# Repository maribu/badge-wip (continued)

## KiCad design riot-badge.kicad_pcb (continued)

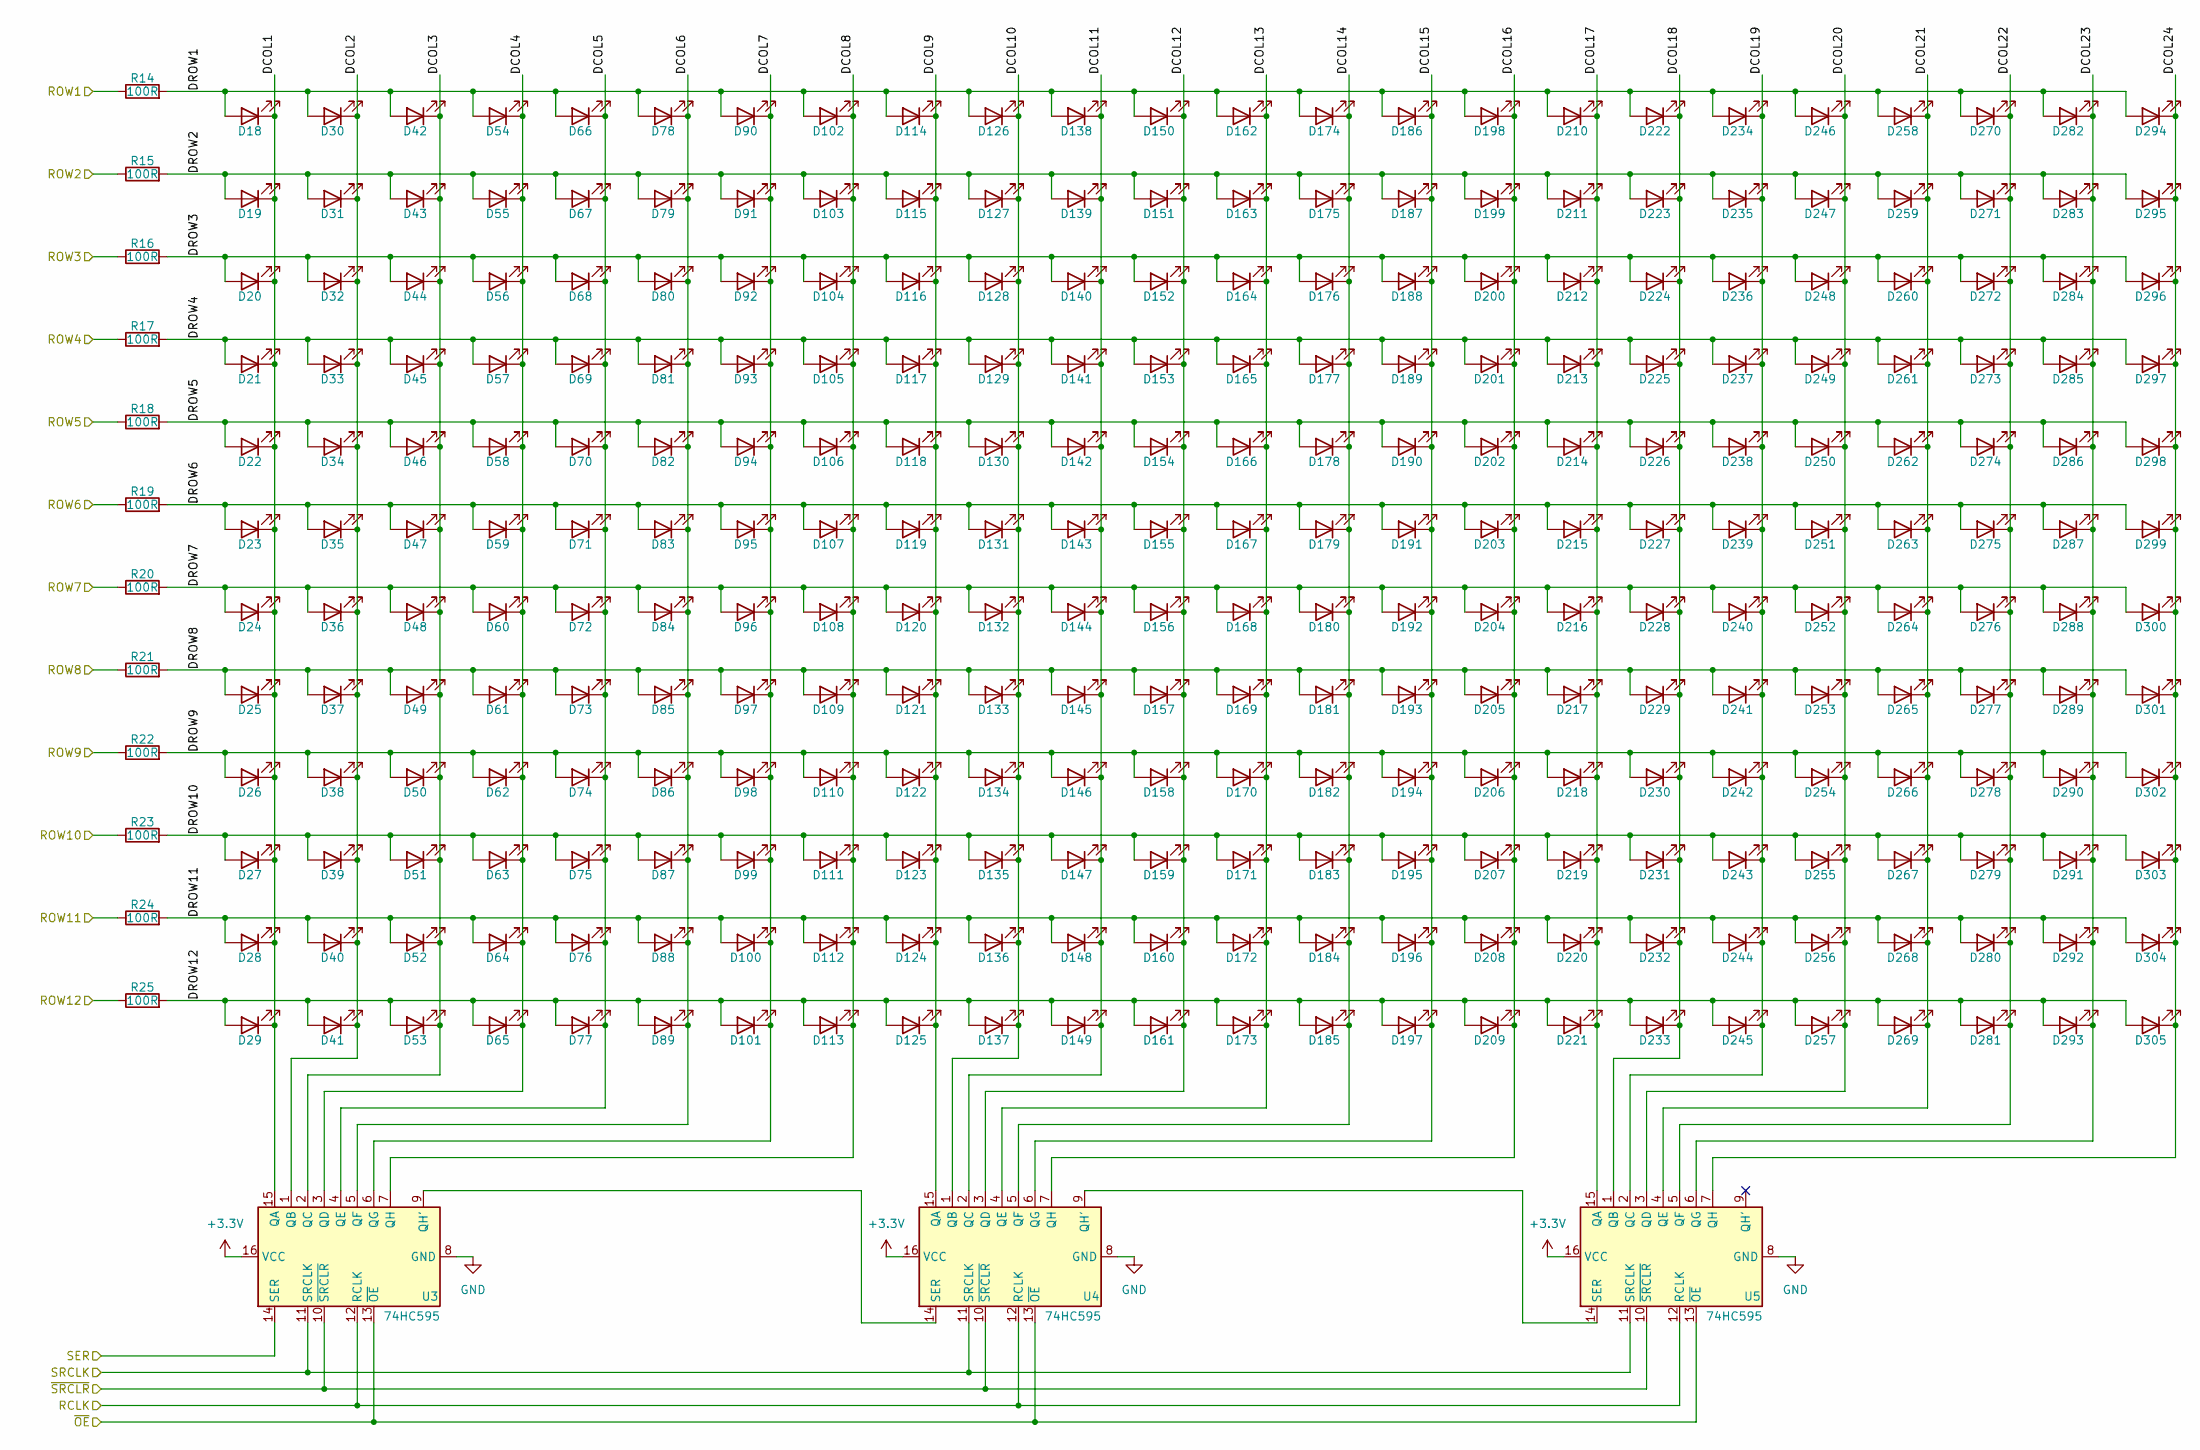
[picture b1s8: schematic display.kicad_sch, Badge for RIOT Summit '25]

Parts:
D18, D19, D20, D21, D22, D23, D24, D25, D26, D27, D28, D29, D30, D31, D32, D33, D34, D35, D36, D37, D38, D39, D40, D41, D42, D43, D44, D45, D46, D47, D48, D49, D50, D51, D52, D53, D54, D55, D56, D57, D58, D59, D60, D61, D62, D63, D64, D65, D66, D67, D68, D69, D70, D71, D72, D73, D74, D75, D76, D77, D78, D79, D80, D81, D82, D83, D84, D85, D86, D87, D88, D89, D90, D91, D92, D93, D94, D95, D96, D97, D98, D99, D100, D101, D102, D103, D104, D105, D106, D107, D108, D109, D110, D111, D112, D113, D114, D115, D116, D117, D118, D119, D120, D121, D122, D123, D124, D125, D126, D127, D128, D129, D130, D131, D132, D133, D134, D135, D136, D137, D138, D139, D140, D141, D142, D143, D144, D145, D146, D147, D148, D149, D150, D151, D152, D153, D154, D155, D156, D157, D158, D159, D160, D161, D162, D163, D164, D165, D166, D167, D168, D169, D170, D171, D172, D173, D174, D175, D176, D177, D178, D179, D180, D181, D182, D183, D184, D185, D186, D187, D188, D189, D190, D191, D192, D193, D194, D195, D196, D197, D198, D199, D200, D201, D202, D203, D204, D205, D206, D207, D208, D209, D210, D211, D212, D213, D214, D215, D216, D217, D218, D219, D220, D221, D222, D223, D224, D225, D226, D227, D228, D229, D230, D231, D232, D233, D234, D235, D236, D237, D238, D239, D240, D241, D242, D243, D244, D245, D246, D247, D248, D249, D250, D251, D252, D253, D254, D255, D256, D257, D258, D259, D260, D261, D262, D263, D264, D265, D266, D267, D268, D269, D270, D271, D272, D273, D274, D275, D276, D277, D278, D279, D280, D281, D282, D283, D284, D285, D286, D287, D288, D289, D290, D291, D292, D293, D294, D295, D296, D297, D298, D299, D300, D301, D302, D303, D304, D305: LED-White; LED_0603_1608Metric; LCSC C2290
R14, R15, R16, R17, R18, R19, R20, R21, R22, R23, R24, R25: 100R; R_0402_1005Metric; LCSC C25076
U3, U4, U5: 74HC595; SOIC-16_3.9x9.9mm_P1.27mm; LCSC C5947

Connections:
+3.3V: U3.16 (VCC), U4.16 (VCC), U5.16 (VCC); also elsewhere on the board
/DISP_RCLK: U3.12 (RCLK), U4.12 (RCLK), U5.12 (RCLK); also elsewhere on the board
/DISP_ROW1: R14.1; also elsewhere on the board
/DISP_ROW2: R15.1; also elsewhere on the board
/DISP_ROW3: R16.1; also elsewhere on the board
/DISP_ROW4: R17.1; also elsewhere on the board
/DISP_ROW5: R18.1; also elsewhere on the board
/DISP_ROW6: R19.1; also elsewhere on the board
/DISP_ROW7: R20.1; also elsewhere on the board
/DISP_ROW8: R21.1; also elsewhere on the board
/DISP_ROW9: R22.1; also elsewhere on the board
/DISP_ROW10: R23.1; also elsewhere on the board
/DISP_ROW11: R24.1; also elsewhere on the board
/DISP_ROW12: R25.1; also elsewhere on the board
/DISP_SER: U3.14 (SER); also elsewhere on the board
/DISP_SRCLK: U3.11 (SRCLK), U4.11 (SRCLK), U5.11 (SRCLK); also elsewhere on the board
/DISP_~SRCLR: U3.10 (~SRCLR), U4.10 (~SRCLR), U5.10 (~SRCLR); also elsewhere on the board
/Display/DCOL1: D18.1 (K), D19.1 (K), D20.1 (K), D21.1 (K), D22.1 (K), D23.1 (K), D24.1 (K), D25.1 (K), D26.1 (K), D27.1 (K), D28.1 (K), D29.1 (K), U3.15 (QA)
/Display/DCOL2: D30.1 (K), D31.1 (K), D32.1 (K), D33.1 (K), D34.1 (K), D35.1 (K), D36.1 (K), D37.1 (K), D38.1 (K), D39.1 (K), D40.1 (K), D41.1 (K), U3.1 (QB)
/Display/DCOL3: D42.1 (K), D43.1 (K), D44.1 (K), D45.1 (K), D46.1 (K), D47.1 (K), D48.1 (K), D49.1 (K), D50.1 (K), D51.1 (K), D52.1 (K), D53.1 (K), U3.2 (QC)
/Display/DCOL4: D54.1 (K), D55.1 (K), D56.1 (K), D57.1 (K), D58.1 (K), D59.1 (K), D60.1 (K), D61.1 (K), D62.1 (K), D63.1 (K), D64.1 (K), D65.1 (K), U3.3 (QD)
/Display/DCOL5: D66.1 (K), D67.1 (K), D68.1 (K), D69.1 (K), D70.1 (K), D71.1 (K), D72.1 (K), D73.1 (K), D74.1 (K), D75.1 (K), D76.1 (K), D77.1 (K), U3.4 (QE)
/Display/DCOL6: D78.1 (K), D79.1 (K), D80.1 (K), D81.1 (K), D82.1 (K), D83.1 (K), D84.1 (K), D85.1 (K), D86.1 (K), D87.1 (K), D88.1 (K), D89.1 (K), U3.5 (QF)
/Display/DCOL7: D90.1 (K), D91.1 (K), D92.1 (K), D93.1 (K), D94.1 (K), D95.1 (K), D96.1 (K), D97.1 (K), D98.1 (K), D99.1 (K), D100.1 (K), D101.1 (K), U3.6 (QG)
/Display/DCOL8: D102.1 (K), D103.1 (K), D104.1 (K), D105.1 (K), D106.1 (K), D107.1 (K), D108.1 (K), D109.1 (K), D110.1 (K), D111.1 (K), D112.1 (K), D113.1 (K), U3.7 (QH)
/Display/DCOL9: D114.1 (K), D115.1 (K), D116.1 (K), D117.1 (K), D118.1 (K), D119.1 (K), D120.1 (K), D121.1 (K), D122.1 (K), D123.1 (K), D124.1 (K), D125.1 (K), U4.15 (QA)
/Display/DCOL10: D126.1 (K), D127.1 (K), D128.1 (K), D129.1 (K), D130.1 (K), D131.1 (K), D132.1 (K), D133.1 (K), D134.1 (K), D135.1 (K), D136.1 (K), D137.1 (K), U4.1 (QB)
/Display/DCOL11: D138.1 (K), D139.1 (K), D140.1 (K), D141.1 (K), D142.1 (K), D143.1 (K), D144.1 (K), D145.1 (K), D146.1 (K), D147.1 (K), D148.1 (K), D149.1 (K), U4.2 (QC)
/Display/DCOL12: D150.1 (K), D151.1 (K), D152.1 (K), D153.1 (K), D154.1 (K), D155.1 (K), D156.1 (K), D157.1 (K), D158.1 (K), D159.1 (K), D160.1 (K), D161.1 (K), U4.3 (QD)
/Display/DCOL13: D162.1 (K), D163.1 (K), D164.1 (K), D165.1 (K), D166.1 (K), D167.1 (K), D168.1 (K), D169.1 (K), D170.1 (K), D171.1 (K), D172.1 (K), D173.1 (K), U4.4 (QE)
/Display/DCOL14: D174.1 (K), D175.1 (K), D176.1 (K), D177.1 (K), D178.1 (K), D179.1 (K), D180.1 (K), D181.1 (K), D182.1 (K), D183.1 (K), D184.1 (K), D185.1 (K), U4.5 (QF)
/Display/DCOL15: D186.1 (K), D187.1 (K), D188.1 (K), D189.1 (K), D190.1 (K), D191.1 (K), D192.1 (K), D193.1 (K), D194.1 (K), D195.1 (K), D196.1 (K), D197.1 (K), U4.6 (QG)
/Display/DCOL16: D198.1 (K), D199.1 (K), D200.1 (K), D201.1 (K), D202.1 (K), D203.1 (K), D204.1 (K), D205.1 (K), D206.1 (K), D207.1 (K), D208.1 (K), D209.1 (K), U4.7 (QH)
/Display/DCOL17: D210.1 (K), D211.1 (K), D212.1 (K), D213.1 (K), D214.1 (K), D215.1 (K), D216.1 (K), D217.1 (K), D218.1 (K), D219.1 (K), D220.1 (K), D221.1 (K), U5.15 (QA)
/Display/DCOL18: D222.1 (K), D223.1 (K), D224.1 (K), D225.1 (K), D226.1 (K), D227.1 (K), D228.1 (K), D229.1 (K), D230.1 (K), D231.1 (K), D232.1 (K), D233.1 (K), U5.1 (QB)
/Display/DCOL19: D234.1 (K), D235.1 (K), D236.1 (K), D237.1 (K), D238.1 (K), D239.1 (K), D240.1 (K), D241.1 (K), D242.1 (K), D243.1 (K), D244.1 (K), D245.1 (K), U5.2 (QC)
/Display/DCOL20: D246.1 (K), D247.1 (K), D248.1 (K), D249.1 (K), D250.1 (K), D251.1 (K), D252.1 (K), D253.1 (K), D254.1 (K), D255.1 (K), D256.1 (K), D257.1 (K), U5.3 (QD)
/Display/DCOL21: D258.1 (K), D259.1 (K), D260.1 (K), D261.1 (K), D262.1 (K), D263.1 (K), D264.1 (K), D265.1 (K), D266.1 (K), D267.1 (K), D268.1 (K), D269.1 (K), U5.4 (QE)
/Display/DCOL22: D270.1 (K), D271.1 (K), D272.1 (K), D273.1 (K), D274.1 (K), D275.1 (K), D276.1 (K), D277.1 (K), D278.1 (K), D279.1 (K), D280.1 (K), D281.1 (K), U5.5 (QF)
/Display/DCOL23: D282.1 (K), D283.1 (K), D284.1 (K), D285.1 (K), D286.1 (K), D287.1 (K), D288.1 (K), D289.1 (K), D290.1 (K), D291.1 (K), D292.1 (K), D293.1 (K), U5.6 (QG)
/Display/DCOL24: D294.1 (K), D295.1 (K), D296.1 (K), D297.1 (K), D298.1 (K), D299.1 (K), D300.1 (K), D301.1 (K), D302.1 (K), D303.1 (K), D304.1 (K), D305.1 (K), U5.7 (QH)
/Display/DROW1: D18.2 (A), D30.2 (A), D42.2 (A), D54.2 (A), D66.2 (A), D78.2 (A), D90.2 (A), D102.2 (A), D114.2 (A), D126.2 (A), D138.2 (A), D150.2 (A), D162.2 (A), D174.2 (A), D186.2 (A), D198.2 (A), D210.2 (A), D222.2 (A), D234.2 (A), D246.2 (A), D258.2 (A), D270.2 (A), D282.2 (A), D294.2 (A), R14.2
/Display/DROW2: D19.2 (A), D31.2 (A), D43.2 (A), D55.2 (A), D67.2 (A), D79.2 (A), D91.2 (A), D103.2 (A), D115.2 (A), D127.2 (A), D139.2 (A), D151.2 (A), D163.2 (A), D175.2 (A), D187.2 (A), D199.2 (A), D211.2 (A), D223.2 (A), D235.2 (A), D247.2 (A), D259.2 (A), D271.2 (A), D283.2 (A), D295.2 (A), R15.2
/Display/DROW3: D20.2 (A), D32.2 (A), D44.2 (A), D56.2 (A), D68.2 (A), D80.2 (A), D92.2 (A), D104.2 (A), D116.2 (A), D128.2 (A), D140.2 (A), D152.2 (A), D164.2 (A), D176.2 (A), D188.2 (A), D200.2 (A), D212.2 (A), D224.2 (A), D236.2 (A), D248.2 (A), D260.2 (A), D272.2 (A), D284.2 (A), D296.2 (A), R16.2
/Display/DROW4: D21.2 (A), D33.2 (A), D45.2 (A), D57.2 (A), D69.2 (A), D81.2 (A), D93.2 (A), D105.2 (A), D117.2 (A), D129.2 (A), D141.2 (A), D153.2 (A), D165.2 (A), D177.2 (A), D189.2 (A), D201.2 (A), D213.2 (A), D225.2 (A), D237.2 (A), D249.2 (A), D261.2 (A), D273.2 (A), D285.2 (A), D297.2 (A), R17.2
/Display/DROW5: D22.2 (A), D34.2 (A), D46.2 (A), D58.2 (A), D70.2 (A), D82.2 (A), D94.2 (A), D106.2 (A), D118.2 (A), D130.2 (A), D142.2 (A), D154.2 (A), D166.2 (A), D178.2 (A), D190.2 (A), D202.2 (A), D214.2 (A), D226.2 (A), D238.2 (A), D250.2 (A), D262.2 (A), D274.2 (A), D286.2 (A), D298.2 (A), R18.2
/Display/DROW6: D23.2 (A), D35.2 (A), D47.2 (A), D59.2 (A), D71.2 (A), D83.2 (A), D95.2 (A), D107.2 (A), D119.2 (A), D131.2 (A), D143.2 (A), D155.2 (A), D167.2 (A), D179.2 (A), D191.2 (A), D203.2 (A), D215.2 (A), D227.2 (A), D239.2 (A), D251.2 (A), D263.2 (A), D275.2 (A), D287.2 (A), D299.2 (A), R19.2
/Display/DROW7: D24.2 (A), D36.2 (A), D48.2 (A), D60.2 (A), D72.2 (A), D84.2 (A), D96.2 (A), D108.2 (A), D120.2 (A), D132.2 (A), D144.2 (A), D156.2 (A), D168.2 (A), D180.2 (A), D192.2 (A), D204.2 (A), D216.2 (A), D228.2 (A), D240.2 (A), D252.2 (A), D264.2 (A), D276.2 (A), D288.2 (A), D300.2 (A), R20.2
/Display/DROW8: D25.2 (A), D37.2 (A), D49.2 (A), D61.2 (A), D73.2 (A), D85.2 (A), D97.2 (A), D109.2 (A), D121.2 (A), D133.2 (A), D145.2 (A), D157.2 (A), D169.2 (A), D181.2 (A), D193.2 (A), D205.2 (A), D217.2 (A), D229.2 (A), D241.2 (A), D253.2 (A), D265.2 (A), D277.2 (A), D289.2 (A), D301.2 (A), R21.2
/Display/DROW9: D26.2 (A), D38.2 (A), D50.2 (A), D62.2 (A), D74.2 (A), D86.2 (A), D98.2 (A), D110.2 (A), D122.2 (A), D134.2 (A), D146.2 (A), D158.2 (A), D170.2 (A), D182.2 (A), D194.2 (A), D206.2 (A), D218.2 (A), D230.2 (A), D242.2 (A), D254.2 (A), D266.2 (A), D278.2 (A), D290.2 (A), D302.2 (A), R22.2
/Display/DROW10: D27.2 (A), D39.2 (A), D51.2 (A), D63.2 (A), D75.2 (A), D87.2 (A), D99.2 (A), D111.2 (A), D123.2 (A), D135.2 (A), D147.2 (A), D159.2 (A), D171.2 (A), D183.2 (A), D195.2 (A), D207.2 (A), D219.2 (A), D231.2 (A), D243.2 (A), D255.2 (A), D267.2 (A), D279.2 (A), D291.2 (A), D303.2 (A), R23.2
/Display/DROW11: D28.2 (A), D40.2 (A), D52.2 (A), D64.2 (A), D76.2 (A), D88.2 (A), D100.2 (A), D112.2 (A), D124.2 (A), D136.2 (A), D148.2 (A), D160.2 (A), D172.2 (A), D184.2 (A), D196.2 (A), D208.2 (A), D220.2 (A), D232.2 (A), D244.2 (A), D256.2 (A), D268.2 (A), D280.2 (A), D292.2 (A), D304.2 (A), R24.2
/Display/DROW12: D29.2 (A), D41.2 (A), D53.2 (A), D65.2 (A), D77.2 (A), D89.2 (A), D101.2 (A), D113.2 (A), D125.2 (A), D137.2 (A), D149.2 (A), D161.2 (A), D173.2 (A), D185.2 (A), D197.2 (A), D209.2 (A), D221.2 (A), D233.2 (A), D245.2 (A), D257.2 (A), D269.2 (A), D281.2 (A), D293.2 (A), D305.2 (A), R25.2
GND: U3.8 (GND), U3.13 (~OE), U4.8 (GND), U4.13 (~OE), U5.8 (GND), U5.13 (~OE); also elsewhere on the board
unnamed: U3.9 (QH'), U4.14 (SER)
unnamed: U4.9 (QH'), U5.14 (SER)

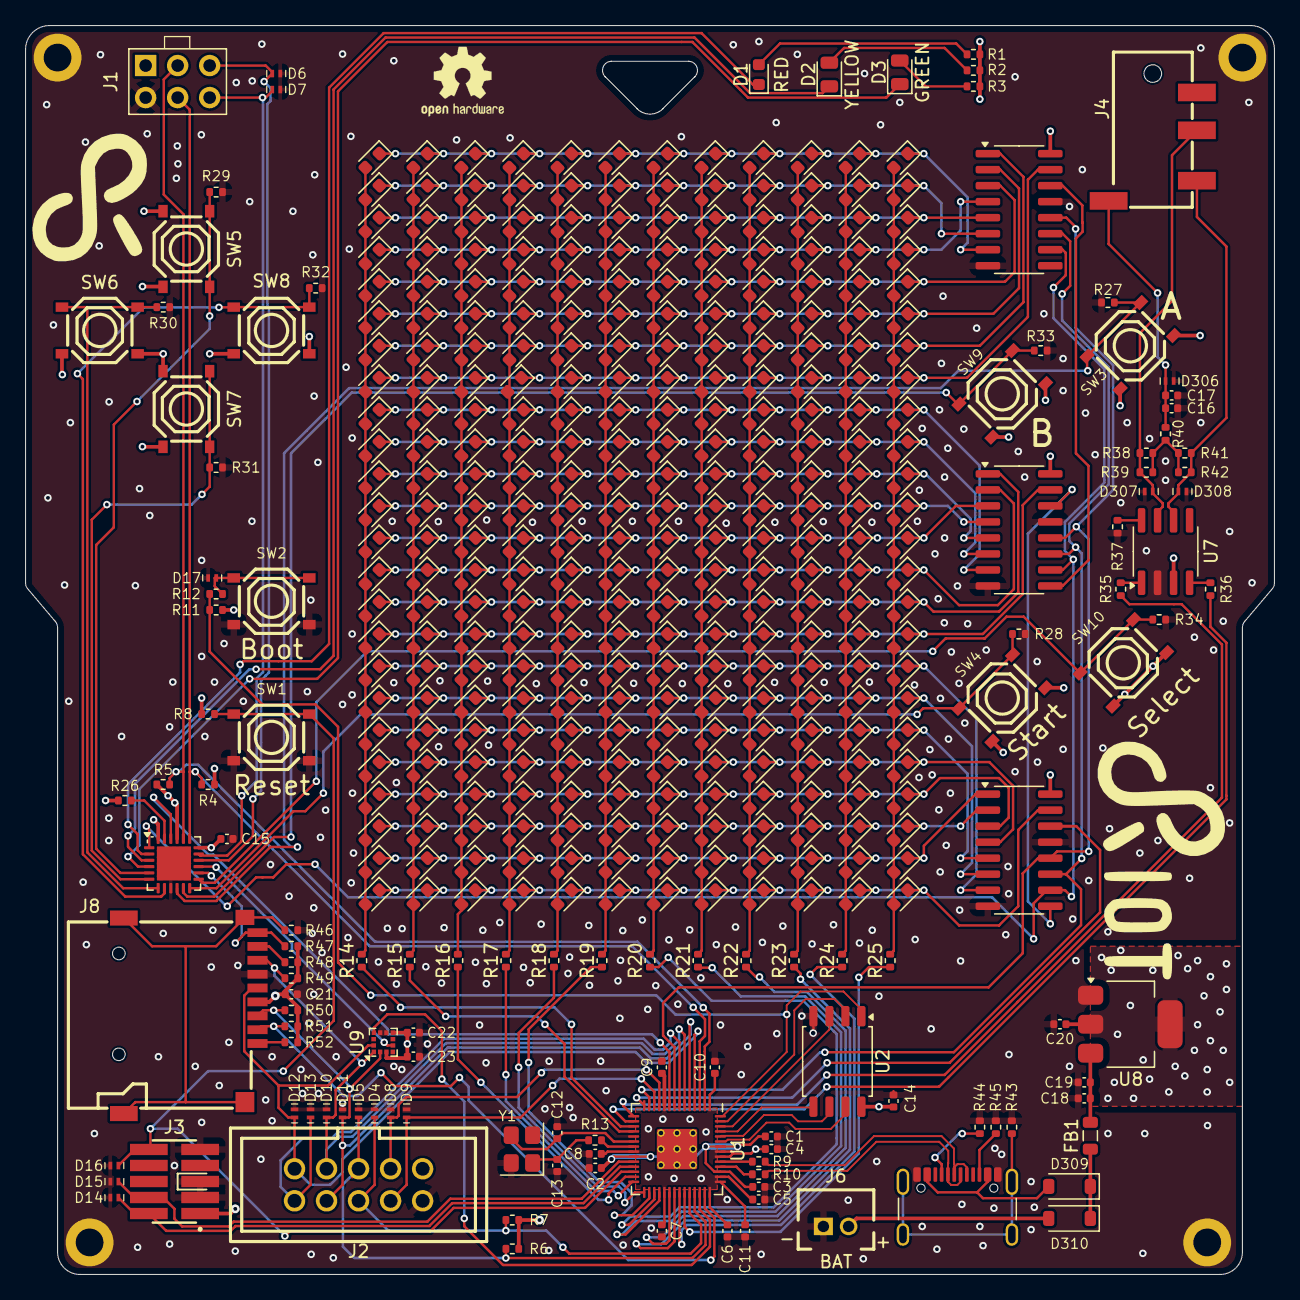
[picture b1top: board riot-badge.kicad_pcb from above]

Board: 4 copper layers, 99.1 x 99.1 mm, 418 parts (0 on the bottom side), 125 nets.

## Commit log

2025-07-28 Add badge schematics
2025-07-29 wip! add concept PCB design
2025-08-04 Updated badge based on feedback from badge.team
2025-08-04 bom: fix using inconsistent value for same part
2025-08-31 Schematics: Add uSD card holder & VBAT sensing
2025-09-04 Schematics: Add accelerometer, drop VBAT sensing
    Adding a cheap accelerometer to the boards, sacraficing the VBAT input
    to make room for the /CS pin.
2025-09-04 board: updated to schematics
2025-09-30 schematic: Fixed LCSC part number for R45
2025-09-30 PCB: Add draft silkscreen decoration
